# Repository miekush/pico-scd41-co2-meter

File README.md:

# Raspberry Pi Pico CO2 Meter

# PCB

Designed by Mike Kushnerik (miekush) in KiCad V6

# License

MKE supports the open source hardware community by sharing hardware design files freely on GitHub!

Please support MKE by purchasing products on [Tindie](https://www.tindie.com/stores/mkengineering/)!

Designed by Mike Kushnerik (miekush)

Licensed under [Creative Commons Attribution-ShareAlike CC BY-SA 4.0](http://creativecommons.org/licenses/by-sa/4.0/)

All text above must be included in any redistribution!

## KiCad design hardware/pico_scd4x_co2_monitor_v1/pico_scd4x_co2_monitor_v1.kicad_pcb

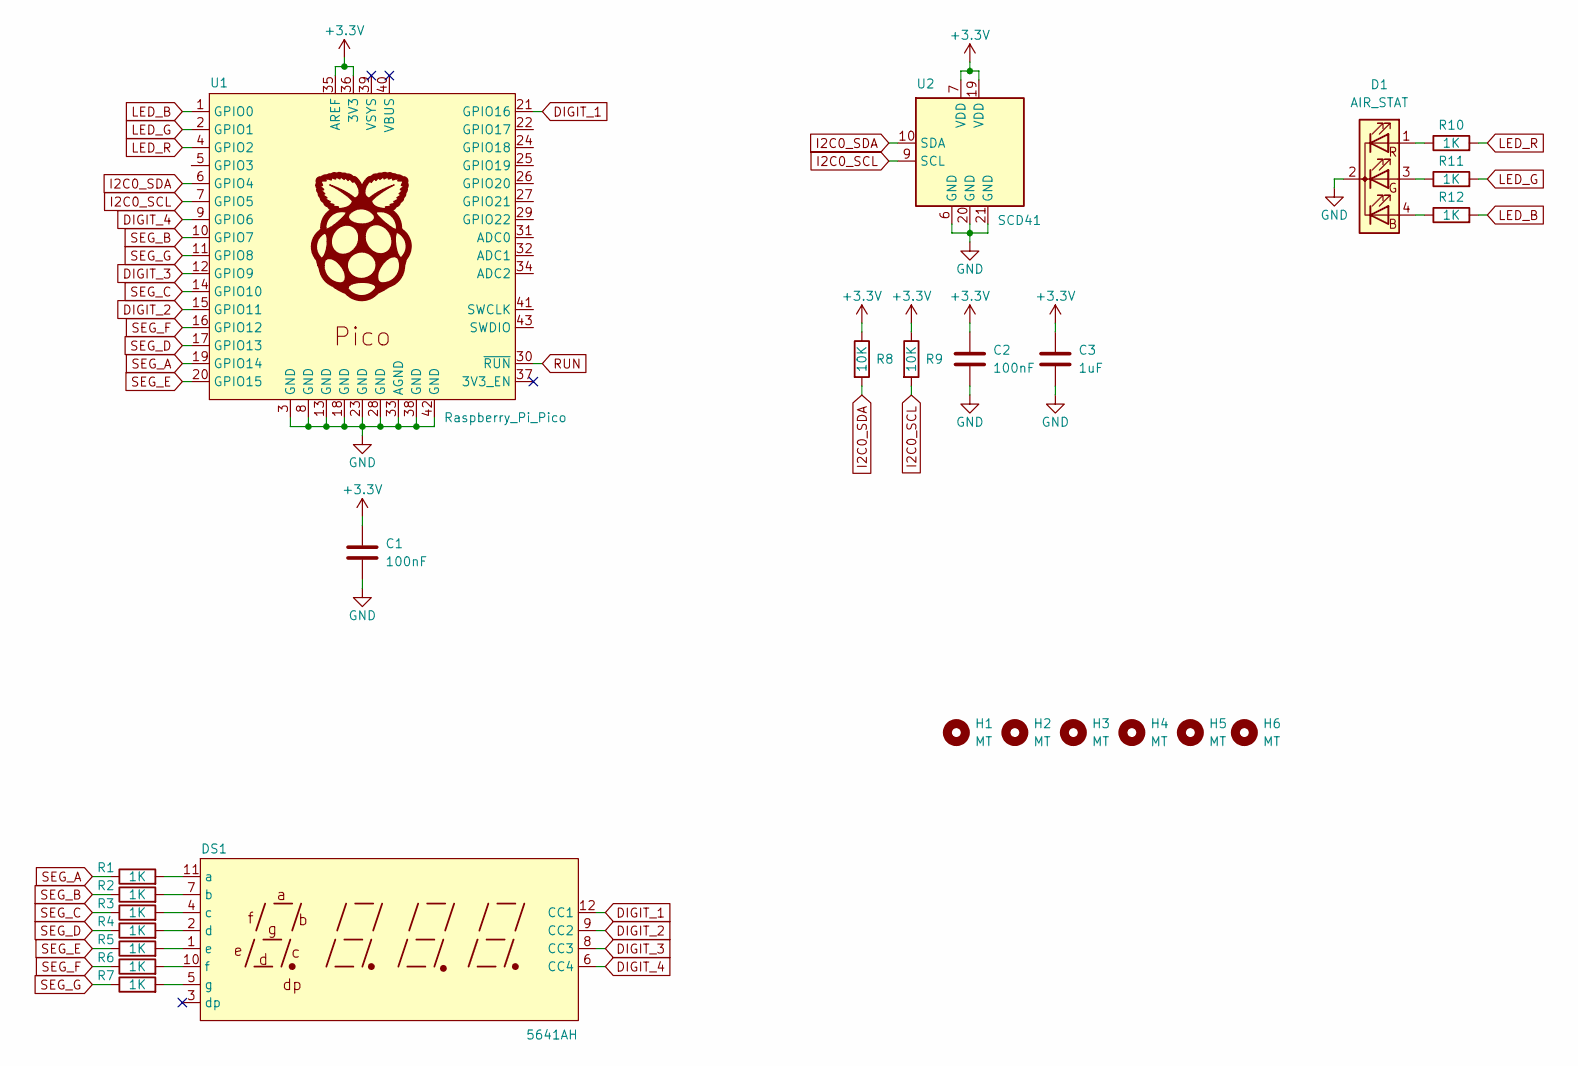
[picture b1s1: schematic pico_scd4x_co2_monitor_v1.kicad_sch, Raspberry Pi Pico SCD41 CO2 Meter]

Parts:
C1, C2: 100nF; C_0603_1608Metric
C3: 1uF; C_0603_1608Metric
D1: AIR_STAT; LED_D5.0mm-4_RGB
DS1: 5641AH
H1, H2, H3, H4, H5, H6: MT; MountingHole_2.2mm_M2
R1, R2, R3, R4, R5, R6, R7, R10, R11, R12: 1K; R_0603_1608Metric
R8, R9: 10K; R_0603_1608Metric
U1: Raspberry_Pi_Pico; RPi_Pico_SMD
U2: SCD41; SCD41DR2

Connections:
+3V3: C1.1, C2.1, C3.1, R8.1, R9.1, U1.35 (AREF), U1.36 (3V3), U2.7 (VDD), U2.19 (VDD)
DIGIT_1: DS1.12 (CC1), U1.21 (GPIO16)
DIGIT_2: DS1.9 (CC2), U1.15 (GPIO11)
DIGIT_3: DS1.8 (CC3), U1.12 (GPIO9)
DIGIT_4: DS1.6 (CC4), U1.9 (GPIO6)
GND: C1.2, C2.2, C3.2, D1.2 (K), U1.3 (GND), U1.8 (GND), U1.13 (GND), U1.18 (GND), U1.23 (GND), U1.28 (GND), U1.33 (AGND), U1.38 (GND), U1.42 (GND), U2.6 (GND), U2.20 (GND), U2.21 (GND)
I2C0_SCL: R9.2, U1.7 (GPIO5), U2.9 (SCL)
I2C0_SDA: R8.2, U1.6 (GPIO4), U2.10 (SDA)
LED_B: R12.2, U1.1 (GPIO0)
LED_G: R11.2, U1.2 (GPIO1)
LED_R: R10.2, U1.4 (GPIO2)
unnamed: D1.1 (RA), R10.1
unnamed: D1.3 (GA), R11.1
unnamed: D1.4 (BA), R12.1
unnamed: DS1.1 (e), R5.2
unnamed: DS1.2 (d), R4.2
unnamed: DS1.4 (c), R3.2
unnamed: DS1.5 (g), R7.2
unnamed: DS1.7 (b), R2.2
unnamed: DS1.10 (f), R6.2
unnamed: DS1.11 (a), R1.2
RUN: U1.30 (~RUN)
SEG_A: R1.1, U1.19 (GPIO14)
SEG_B: R2.1, U1.10 (GPIO7)
SEG_C: R3.1, U1.14 (GPIO10)
SEG_D: R4.1, U1.17 (GPIO13)
SEG_E: R5.1, U1.20 (GPIO15)
SEG_F: R6.1, U1.16 (GPIO12)
SEG_G: R7.1, U1.11 (GPIO8)

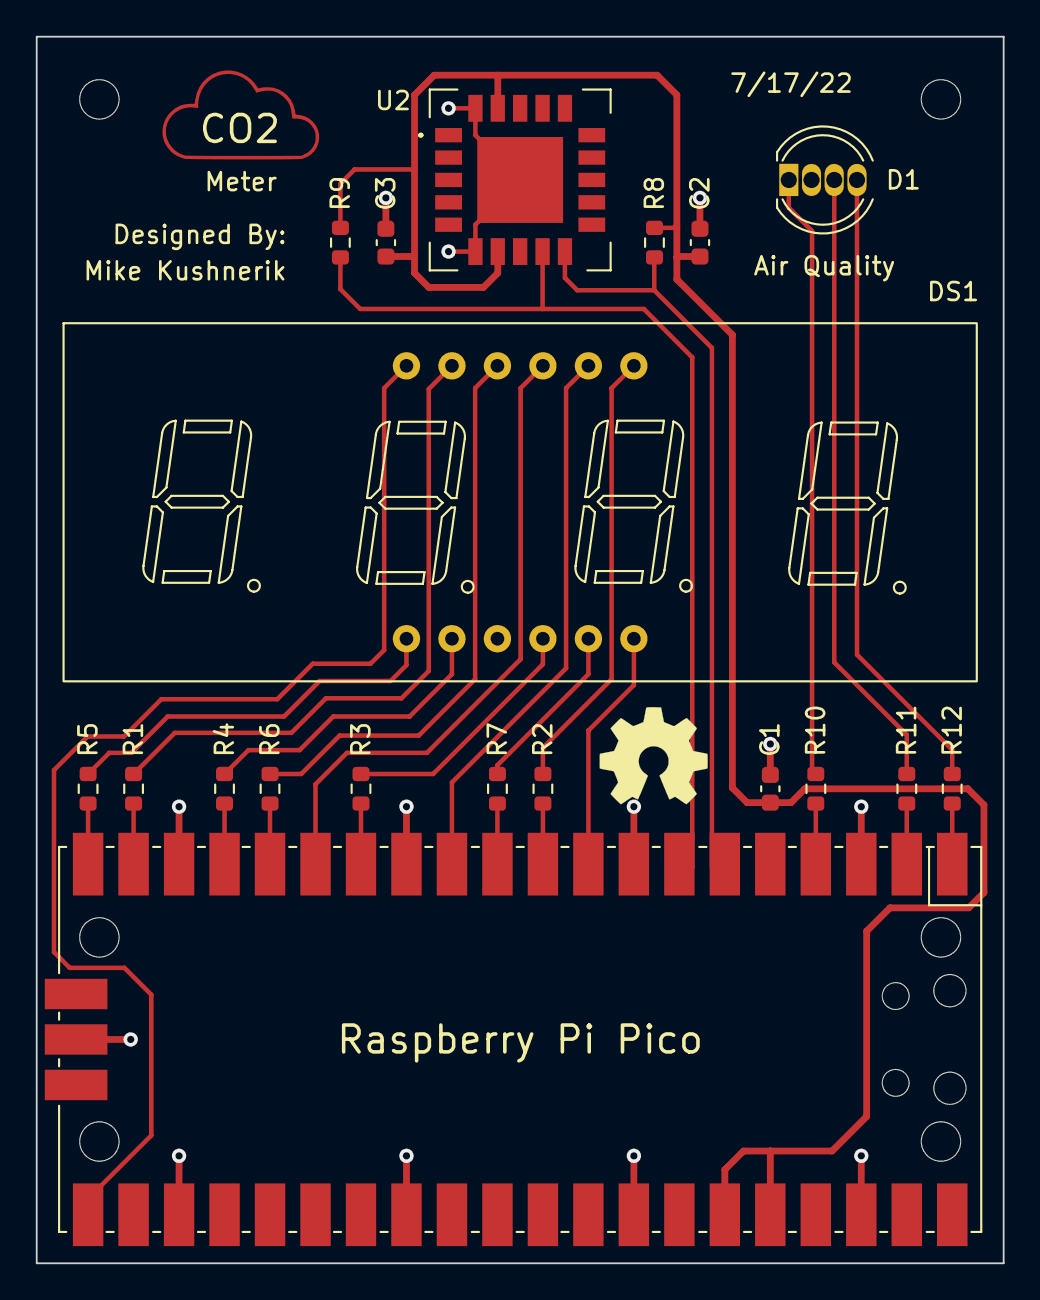
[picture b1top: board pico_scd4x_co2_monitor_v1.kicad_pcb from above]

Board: 2 copper layers, 54.0 x 68.5 mm, 25 parts (0 on the bottom side), 28 nets.

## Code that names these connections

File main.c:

//Raspberry Pi Pico SCD41 7 Segment
//Device: RP2040, SCD41, HS420561K-32 (CC 7-Segment Display)
//File: main.c
//Author: Mike Kushnerik
//Date: 7/15/2022

//I2C Bus Wiring (default):
//SDA = GP4
//SCL = GP5
//see sensirion_i2c_hal_init(void) in "sensirion_i2c_hal.c" to change from default

#include <stdio.h>
#include "scd4x_i2c.h"
#include "sensirion_common.h"
#include "sensirion_i2c_hal.h"
#include "pico/stdlib.h"
#include "hardware/gpio.h"

/* //7 segment wiring (adjust as needed):
#define a_pin       6
#define b_pin       7
#define c_pin       8
#define d_pin       9
#define e_pin       10
#define f_pin       11
#define g_pin       12
#define digit_1     13
#define digit_2     14
#define digit_3     15
#define digit_4     16 */

//7 segment wiring (adjust as needed):
#define a_pin       14
#define b_pin       7
#define c_pin       10
#define d_pin       13
#define e_pin       15
#define f_pin       12
#define g_pin       8
#define digit_1     16
#define digit_2     11
#define digit_3     9
#define digit_4     6

//rgb led pins:
#define led_r       2
#define led_g       1
#define led_b       0

//create mask for segment pins
const uint32_t segment_mask =   (1 << a_pin) |
                                (1 << b_pin) |
                                (1 << c_pin) |
                                (1 << d_pin) |
                                (1 << e_pin) |
                                (1 << f_pin) |
                                (1 << g_pin);

//create mask for digit pins
const uint32_t digit_mask =     (1 << digit_1) |
                                (1 << digit_2) |
                                (1 << digit_3) |
                                (1 << digit_4);

const uint32_t rgb_mask =       (1 << led_r) |
                                (1 << led_g) |
                                (1 << led_b);

//LUT for segment pins
//i.e. segment_pins[5] will display the value 5 on the display digit
const uint32_t segment_pins[10] =
{
    //0
    ((1<<a_pin) | (1<<b_pin) | (1<<c_pin) | (1<<d_pin) | (1<<e_pin) | (1<<f_pin)),
    //1
    ((1<<b_pin) | (1<<c_pin)),
    //2
    ((1<<a_pin) | (1<<b_pin) | (1<<d_pin) | (1<<e_pin) | (1<<g_pin)),
    //3
    ((1<<a_pin) | (1<<b_pin) | (1<<c_pin) | (1<<d_pin) | (1<<g_pin)),
    //4
    ((1<<b_pin) | (1<<c_pin) | (1<<f_pin) | (1<<g_pin)),
    //5
    ((1<<a_pin) | (1<<c_pin) | (1<<d_pin) | (1<<f_pin) | (1<<g_pin)),
    //6
    ((1<<a_pin) | (1<<c_pin) | (1<<d_pin) | (1<<e_pin) | (1<<f_pin) | (1<<g_pin)),
    //7
    ((1<<a_pin) | (1<<b_pin) | (1<<c_pin)),
    //8
    ((1<<a_pin) | (1<<b_pin) | (1<<c_pin) | (1<<d_pin) | (1<<e_pin) | (1<<f_pin) | (1<<g_pin)),
    //9
    ((1<<a_pin) | (1<<b_pin) | (1<<c_pin) | (1<<d_pin) | (1<<f_pin) | (1<<g_pin))
};

//LUT for digit pins
//i.e. digit_pins[0] is the most significant digit of the display
uint32_t digit_pins[4] =
{
    digit_1,
    digit_2,
    digit_3,
    digit_4
};

uint16_t co2 = 9999;
int32_t temperature = 0;
int32_t humidity = 0;
bool timerFlag = false;

//function prototypes
void init_display(void);
void update_display(uint16_t value);
void init_rgb(void);
void update_rgb(uint16_t value);

bool timer_cb(struct repeating_timer *t);

int main() 
{
    stdio_init_all();
    init_display();
    init_rgb();    

    sensirion_i2c_hal_init();

    scd4x_wake_up();
    scd4x_stop_periodic_measurement();
    scd4x_reinit();

    scd4x_start_periodic_measurement();

    //timer to poll scd41 every 5s
    struct repeating_timer timer;
    add_repeating_timer_ms(5000, timer_cb, NULL, &timer);

    while(1)
    {
        update_display(co2);
        update_rgb(co2);

        if(timerFlag)
        {
            //read scd41
            int16_t error = scd4x_read_measurement(&co2, &temperature, &humidity);
            //clear flag
            timerFlag = false;
        }
    }

    return 0;
}

//function to init the 7 segment display
void init_display(void)
{
    //init 7 segment output pins
    gpio_init_mask(segment_mask | digit_mask);
    //set pins as output
    gpio_set_dir_out_masked(segment_mask | digit_mask);
}

//function to init the rgb led
void init_rgb(void)
{
    //init the rgb output pins
    gpio_init_mask(rgb_mask);
    //set pins as output
    gpio_set_dir_out_masked(rgb_mask);
}

//function to update the value of the 7 segment display
void update_display(uint16_t value)
{
    //turn all digits off
    gpio_put_masked(digit_mask, digit_mask);
    //turn all segments off
    gpio_clr_mask(segment_mask);

    int i = 0;
    do
    {
        //turn all digits off
        gpio_put_masked(digit_mask, digit_mask);
        //select digit
        gpio_put(digit_pins[3-i], 0);
        //write digit value
        gpio_put_masked(segment_mask, segment_pins[value % 10]);
        //2000us seems to work well :p
        sleep_us(2000);
        i++;
    } while (value /= 10);
}

//function to update the air quality RGB led
void update_rgb(uint16_t value)
{
    //good air quality
    if(value < 800)
    {
        gpio_put(led_r, 0);
        gpio_put(led_g, 1);
        gpio_put(led_b, 0);
    }
    //average air quality
    else if (value >= 800 && value < 1000)
    {
        gpio_put(led_r, 1);
        gpio_put(led_g, 1);
        gpio_put(led_b, 0);
    }
    //bad air quality
    else
    {
        gpio_put(led_r, 1);
        gpio_put(led_g, 0);
        gpio_put(led_b, 0);        
    }
}

//timer interrupt callback to poll scd41
bool timer_cb(struct repeating_timer *t)
{
    //set flag
    timerFlag = true;
    return true;
}

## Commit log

2022-07-16 Initial upload
2022-07-18 Add pcb KiCad files
2022-07-18 Add board photo
2022-07-18 Add image
2022-07-18 Resize image
2022-07-31 Add hardware design files
